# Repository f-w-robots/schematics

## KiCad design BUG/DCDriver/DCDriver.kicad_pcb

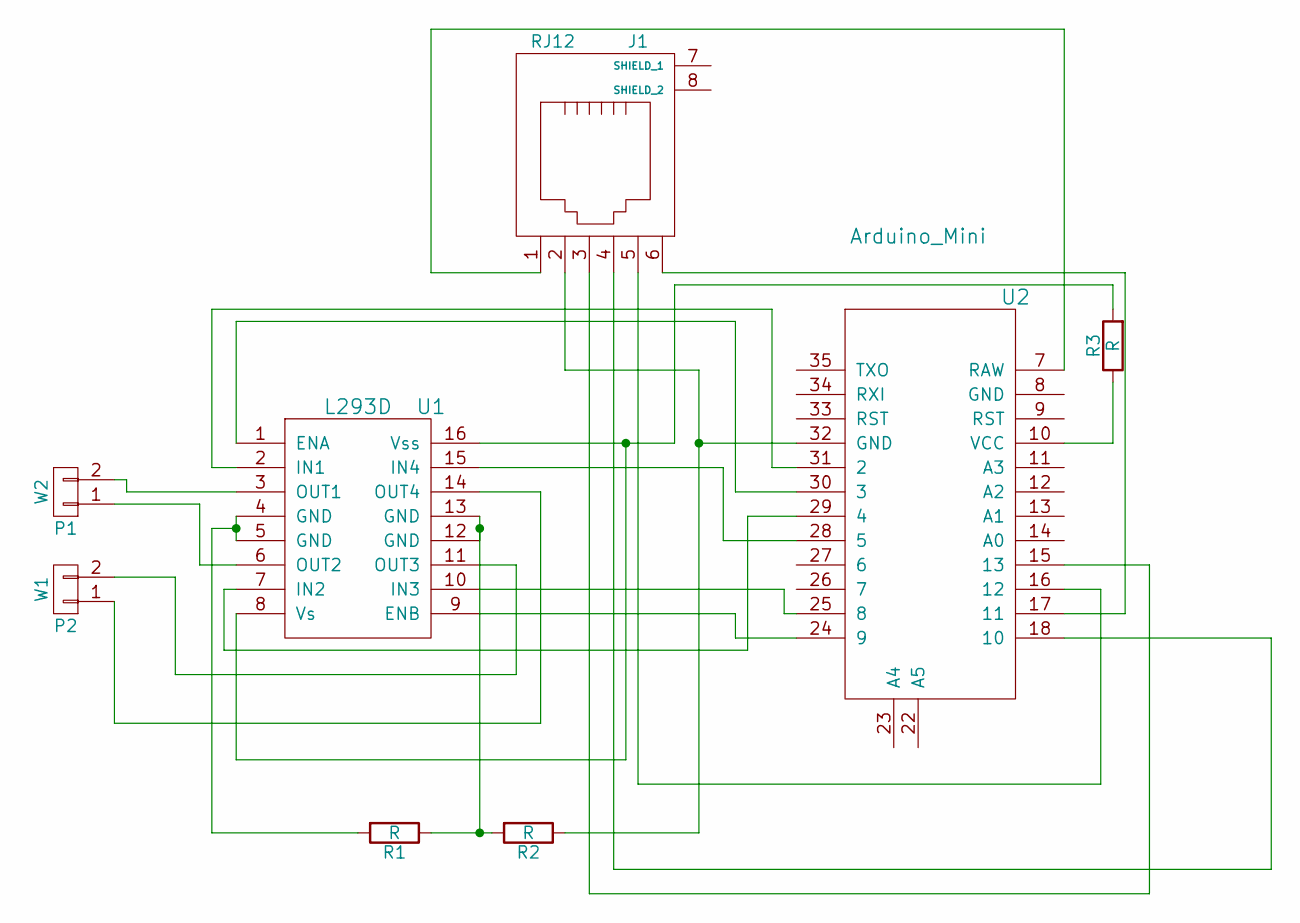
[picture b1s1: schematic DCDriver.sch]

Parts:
J1: RJ12; RJ12_Client
P1: W2; Pin_Header_Straight_1x02
P2: W1; Pin_Header_Straight_1x02
R1, R2, R3: R; R_1206
U1: L293D; DIP-16_W7.62mm
U2: Arduino_Mini; arduino_mini_pro

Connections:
unnamed: J1.1, U2.7 (RAW)
unnamed: J1.2, R2.1, U2.32 (GND)
unnamed: J1.3, U2.15 (13)
unnamed: J1.4, U2.18 (10)
unnamed: J1.5, U2.16 (12)
unnamed: J1.6, U2.17 (11)
unnamed: P1.1, U1.6 (OUT2)
unnamed: P1.2, U1.3 (OUT1)
unnamed: P2.1, U1.14 (OUT4)
unnamed: P2.2, U1.11 (OUT3)
unnamed: R1.1, R2.2, U1.12 (GND), U1.13 (GND)
unnamed: R1.2, U1.4 (GND), U1.5 (GND)
unnamed: R3.1, U2.10 (VCC)
unnamed: R3.2, U1.8 (Vs), U1.16 (Vss)
unnamed: U1.1 (ENA), U2.30 (3)
unnamed: U1.2 (IN1), U2.31 (2)
unnamed: U1.7 (IN2), U2.29 (4)
unnamed: U1.9 (ENB), U2.24 (9)
unnamed: U1.10 (IN3), U2.25 (8)
unnamed: U1.15 (IN4), U2.28 (5)

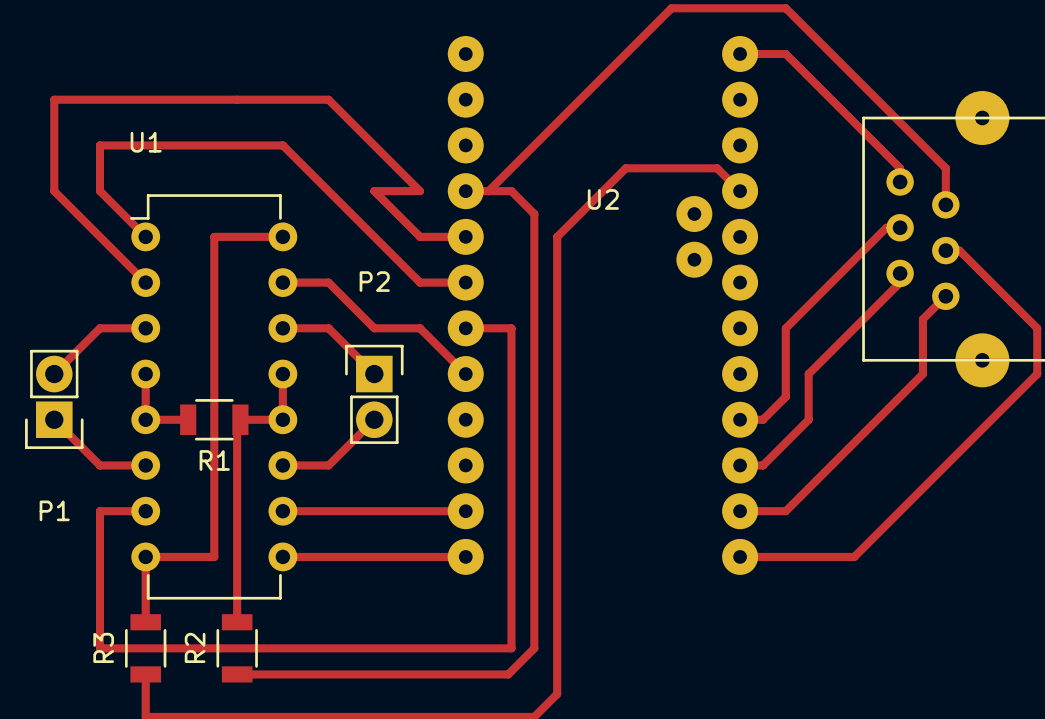
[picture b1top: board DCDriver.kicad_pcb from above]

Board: 2 copper layers, 8 parts (0 on the bottom side), 20 nets.

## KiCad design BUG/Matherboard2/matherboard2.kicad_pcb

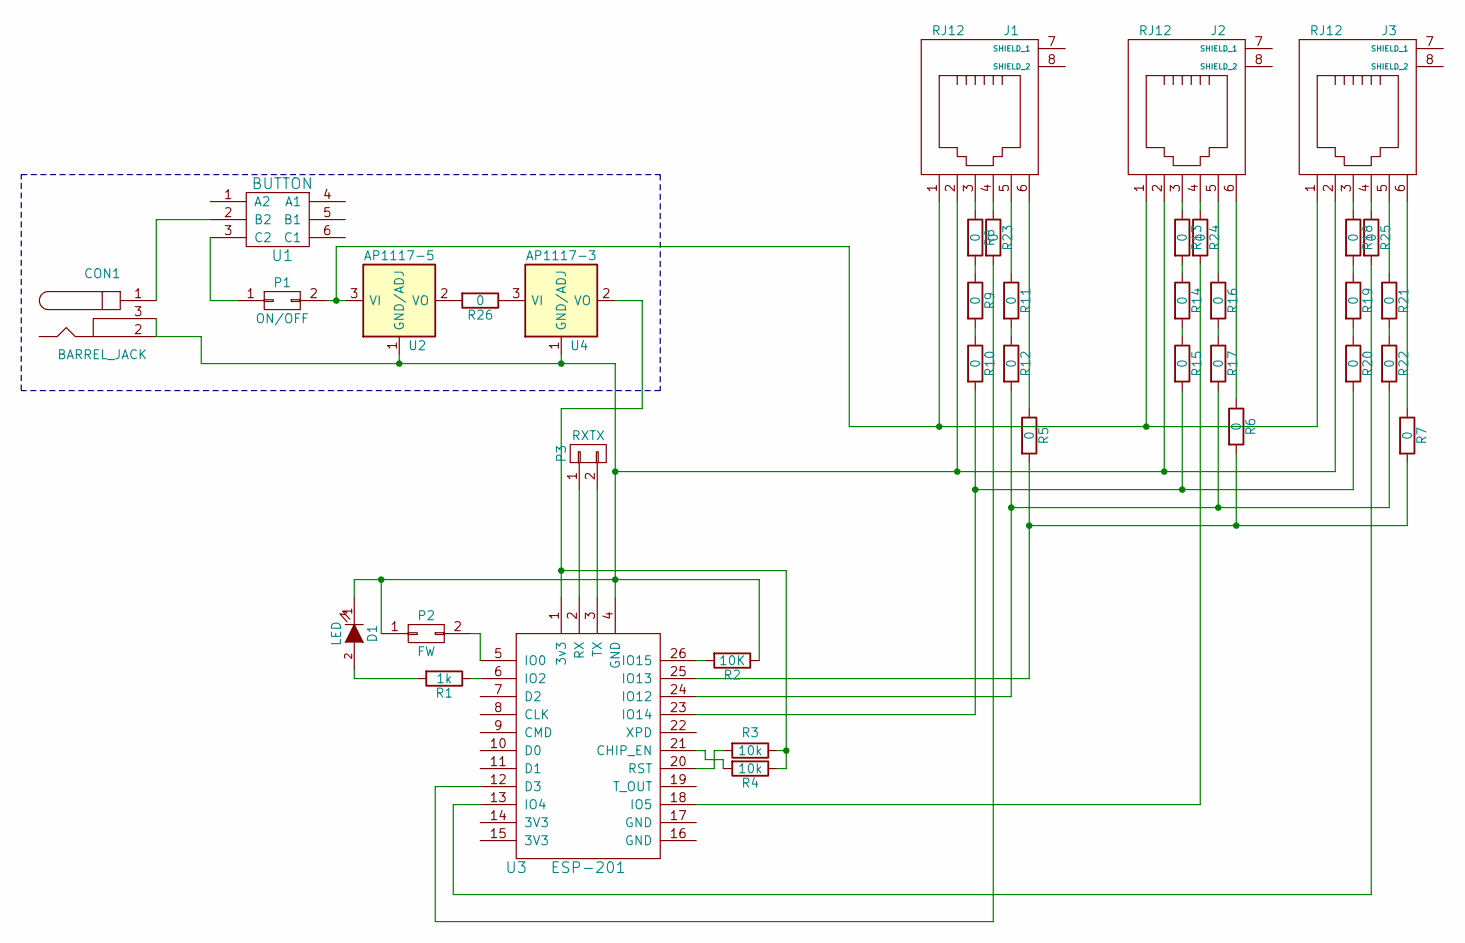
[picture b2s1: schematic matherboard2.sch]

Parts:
CON1: BARREL_JACK
D1: LED; LED-5MM
J1, J2, J3: RJ12; RJ12_E
P1: ON/OFF; Pin_Header_Straight_2x01
P2: FW; Pin_Header_Straight_2x01
P3: RXTX; Pin_Header_Straight_1x02
R1: 1k; Resistor_Horizontal_RM7mm
R2: 10K; Resistor_Horizontal_RM7mm
R3, R4: 10k; Resistor_Horizontal_RM7mm
R5, R6, R7, R8, R9, R10, R11, R12, R13, R14, R15, R16, R17, R18, R19, R20, R21, R22, R23, R24, R25, R26: 0; R_1206
U1: BUTTON; button
U2: AP1117-5; SW_Micro_SPST
U3: ESP-201; ESP201
U4: AP1117-3; SW_Micro_SPST

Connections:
unnamed: CON1.1, U1.2 (B2)
unnamed: CON1.2, CON1.3, D1.1 (K), J1.2, J2.2, J3.2, P2.1, R2.1, U2.1 (GND/ADJ), U3.4 (GND), U4.1 (GND/ADJ)
unnamed: D1.2 (A), R1.2
unnamed: J1.1, J2.1, J3.1, P1.2, U2.3 (VI)
unnamed: J1.3, R8.1
unnamed: J1.4, R23.1
unnamed: J1.5, R11.1
unnamed: J1.6, R5.1
unnamed: J2.3, R13.1
unnamed: J2.4, R24.1
unnamed: J2.5, R16.1
unnamed: J2.6, R6.1
unnamed: J3.3, R18.1
unnamed: J3.4, R25.1
unnamed: J3.5, R21.1
unnamed: J3.6, R7.1
unnamed: P1.1, U1.3 (C2)
unnamed: P2.2, U3.5 (IO0)
unnamed: P3.1, U3.2 (RX)
unnamed: P3.2, U3.3 (TX)
unnamed: R1.1, U3.6 (IO2)
unnamed: R2.2, U3.26 (IO15)
unnamed: R3.1, R4.1, U3.1 (3v3), U4.2 (VO)
unnamed: R3.2, U3.20 (RST)
unnamed: R4.2, U3.21 (CHIP_EN)
unnamed: R5.2, R6.2, R7.2, U3.25 (IO13)
unnamed: R8.2, R9.1
unnamed: R9.2, R10.1
unnamed: R10.2, R15.2, R20.2, U3.23 (IO14)
unnamed: R11.2, R12.1
unnamed: R12.2, R17.2, R22.2, U3.24 (IO12)
unnamed: R13.2, R14.1
unnamed: R14.2, R15.1
unnamed: R16.2, R17.1
unnamed: R18.2, R19.1
unnamed: R19.2, R20.1
unnamed: R21.2, R22.1
unnamed: R23.2, U3.12 (D3)
unnamed: R24.2, U3.18 (IO5)
unnamed: R25.2, U3.13 (IO4)
unnamed: R26.1, U4.3 (VI)
unnamed: R26.2, U2.2 (VO)

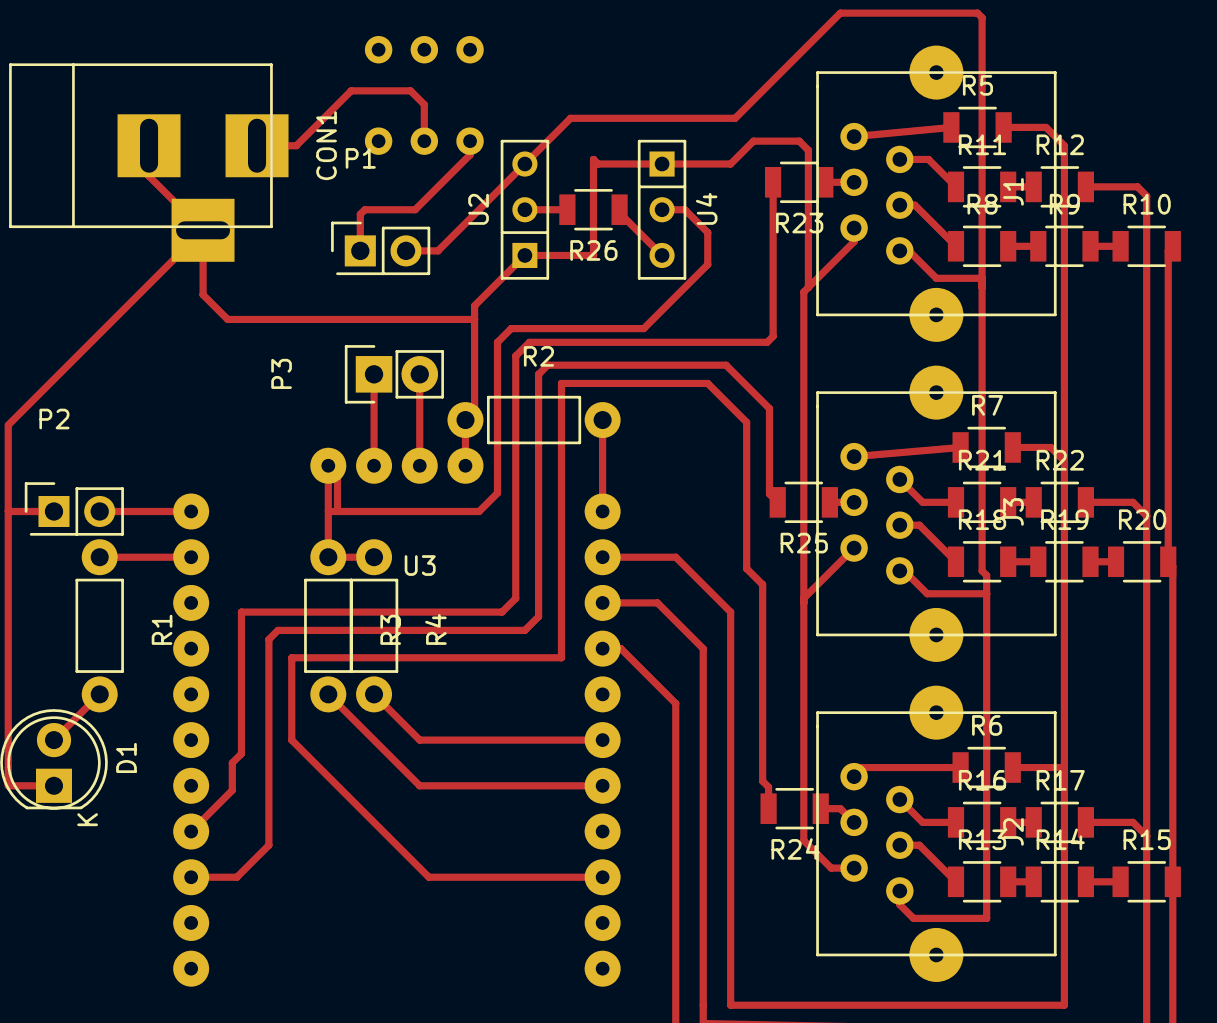
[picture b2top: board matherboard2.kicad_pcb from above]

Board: 2 copper layers, 38 parts (1 on the bottom side), 42 nets.

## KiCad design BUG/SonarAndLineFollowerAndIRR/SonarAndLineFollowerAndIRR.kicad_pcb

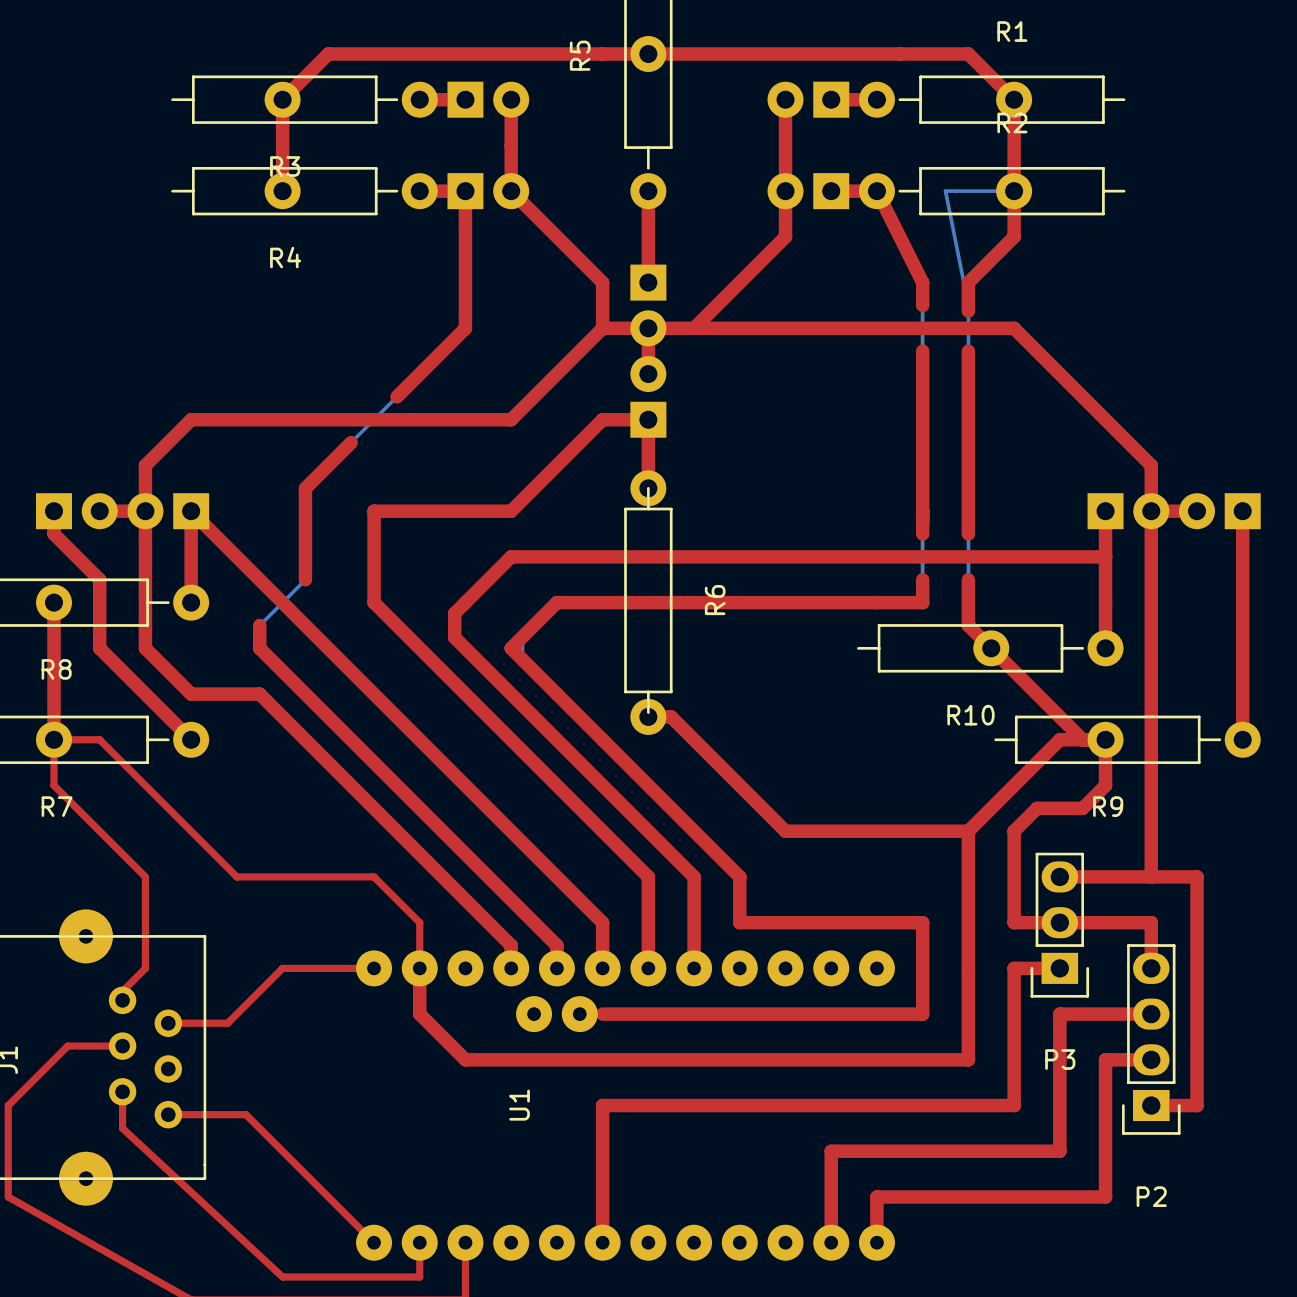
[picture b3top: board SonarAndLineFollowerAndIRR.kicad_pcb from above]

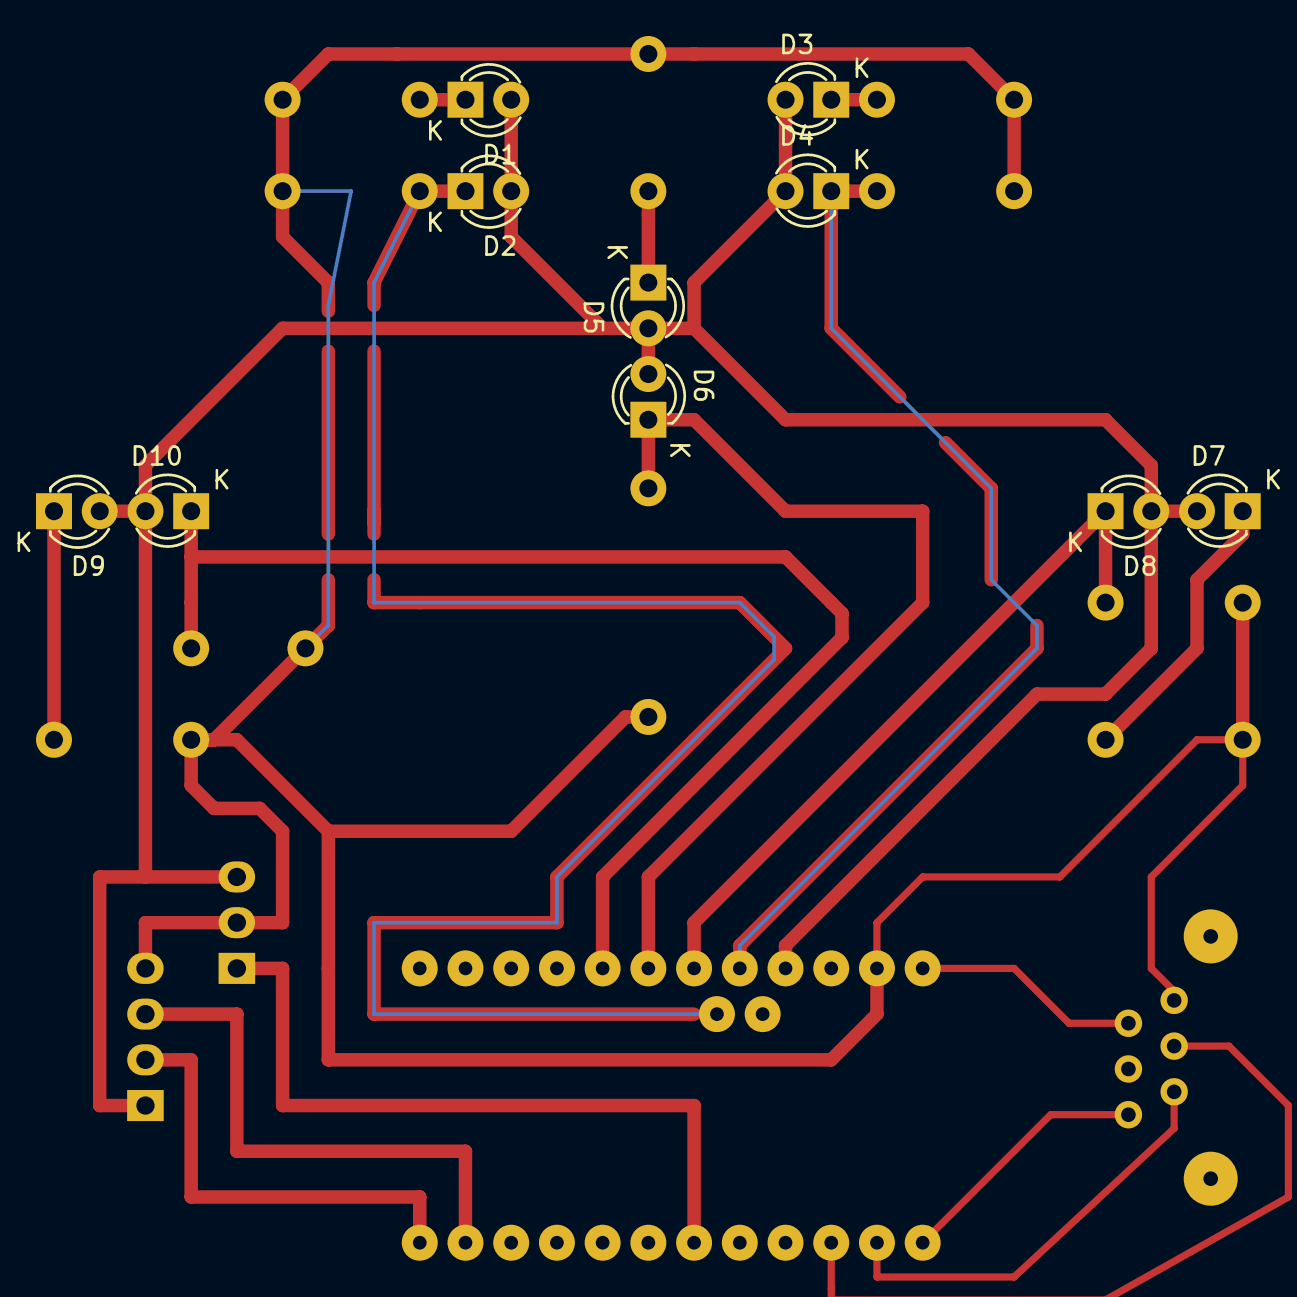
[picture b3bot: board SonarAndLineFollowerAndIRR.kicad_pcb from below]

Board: 2 copper layers, 24 parts (10 on the bottom side), 19 nets.

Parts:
D1, D2, D3, D4, D5, D6, D7, D8, D9, D10: LED; LED-3MM
J1: RJ12; RJ12_Client
P2: Sonar; Pin_Header_Straight_1x04
P3: CONN_01X03; Pin_Header_Straight_1x03
R1, R3, R5, R7, R9: 150; Resistor_Horizontal_RM15mm
R2, R4, R6, R8, R10: 510k; Resistor_Horizontal_RM15mm
U1: Arduino_Mini; arduino_mini_pro

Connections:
unnamed: D1.1, R1.1
unnamed: D1.2, D2.2, D3.2, D4.2, D5.2, D6.2, D7.2, D8.2, D9.2, D10.2, P2.1, P3.3, U1.10
unnamed: D2.1, R2.1, U1.23
unnamed: D3.1, R3.1
unnamed: D4.1, R4.1, U1.11
unnamed: D5.1, R5.1
unnamed: D6.1, R6.1, U1.13
unnamed: D7.1, R7.1
unnamed: D8.1, R8.1, U1.12
unnamed: D9.1, R9.1
unnamed: D10.1, R10.1, U1.14
unnamed: J1.1, U1.35
unnamed: J1.2, U1.34
unnamed: J1.4, U1.33
unnamed: J1.5, U1.7
unnamed: J1.6, P2.4, P3.2, R1.2, R2.2, R3.2, R4.2, R5.2, R6.2, R7.2, R8.2, R9.2, R10.2, U1.8
unnamed: P2.2, U1.24
unnamed: P2.3, U1.25
unnamed: P3.1, U1.30

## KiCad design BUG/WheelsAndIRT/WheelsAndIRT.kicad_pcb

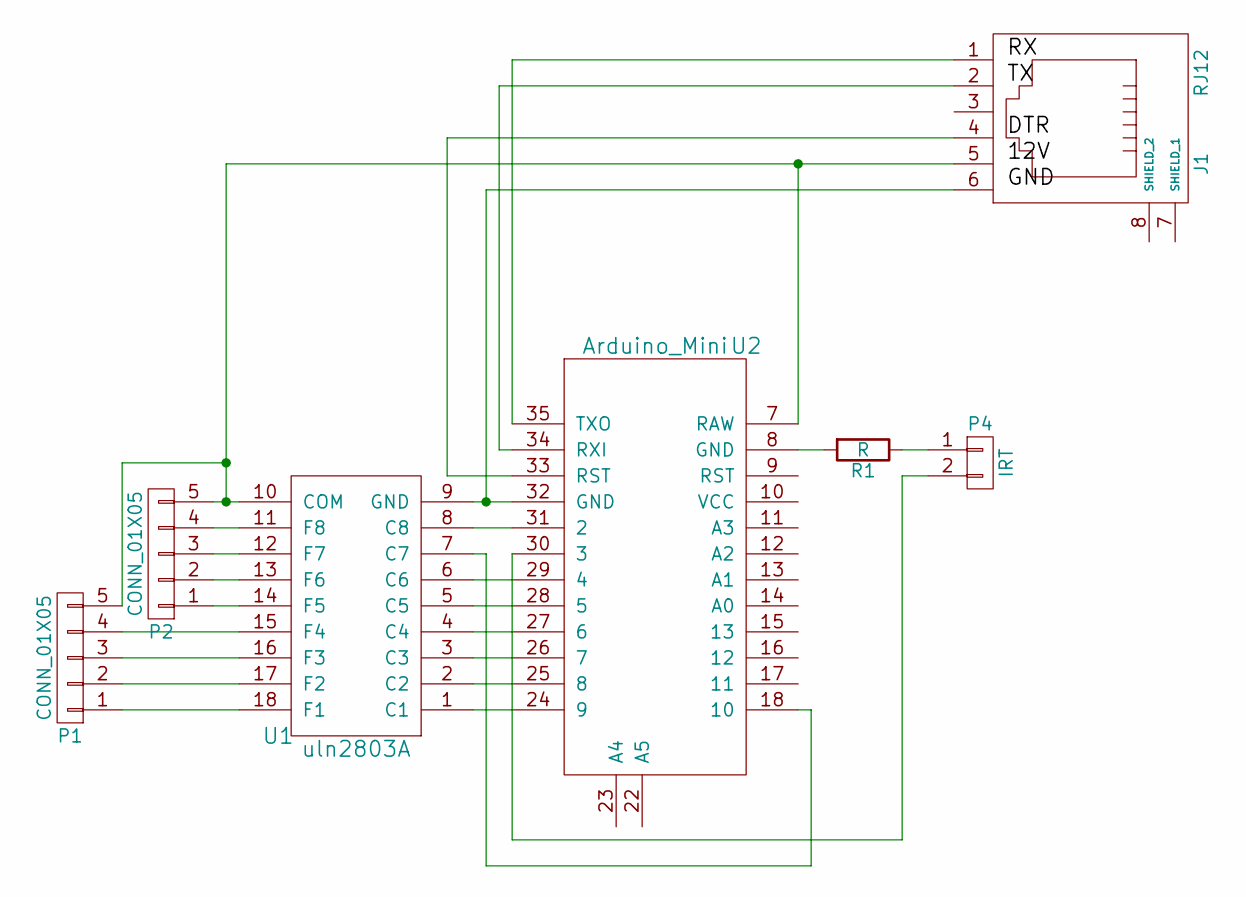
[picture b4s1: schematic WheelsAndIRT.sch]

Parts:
J1: RJ12; RJ12_Client
P1, P2: CONN_01X05; Pin_Header_Straight_1x05
P4: IRT; Pin_Header_Straight_1x02
R1: R; Resistor_Horizontal_RM10mm
U1: uln2803A; DIP-18_W7.62mm
U2: Arduino_Mini; arduino_mini_pro

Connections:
unnamed: J1.1, U2.35 (TXO)
unnamed: J1.2, U2.34 (RXI)
unnamed: J1.4, U2.33 (RST)
unnamed: J1.5, P1.5, P2.5, U1.10 (COM), U2.7 (RAW)
unnamed: J1.6, U1.9 (GND), U2.32 (GND)
unnamed: P1.1, U1.18 (F1)
unnamed: P1.2, U1.17 (F2)
unnamed: P1.3, U1.16 (F3)
unnamed: P1.4, U1.15 (F4)
unnamed: P2.1, U1.14 (F5)
unnamed: P2.2, U1.13 (F6)
unnamed: P2.3, U1.12 (F7)
unnamed: P2.4, U1.11 (F8)
unnamed: P4.1, R1.1
unnamed: P4.2, U2.30 (3)
unnamed: R1.2, U2.8 (GND)
unnamed: U1.1 (C1), U2.24 (9)
unnamed: U1.2 (С2), U2.25 (8)
unnamed: U1.3 (С3), U2.26 (7)
unnamed: U1.4 (С4), U2.27 (6)
unnamed: U1.5 (С5), U2.28 (5)
unnamed: U1.6 (С6), U2.29 (4)
unnamed: U1.7 (С7), U2.18 (10)
unnamed: U1.8 (С8), U2.31 (2)

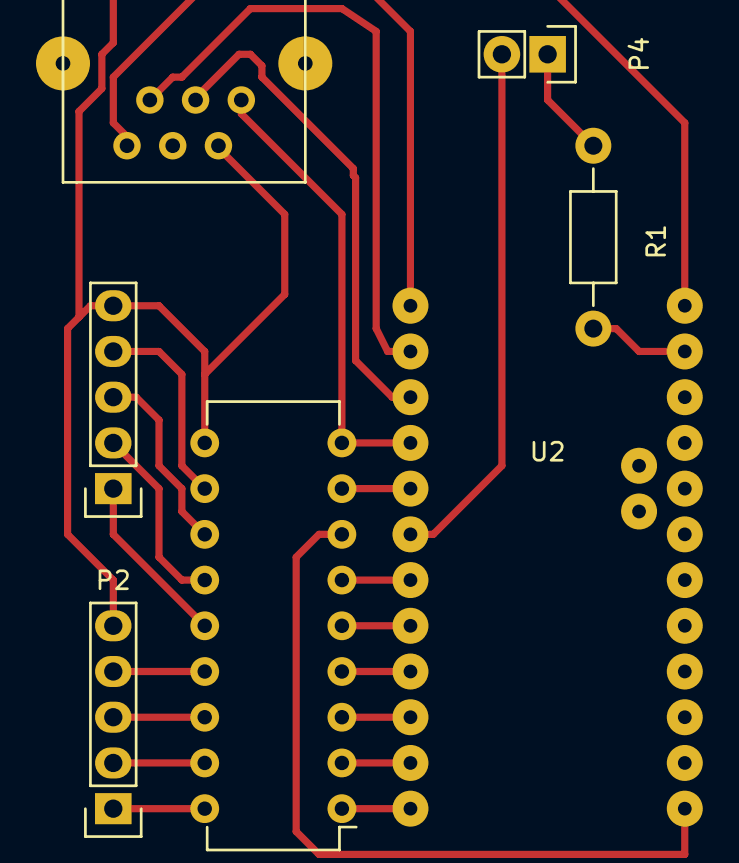
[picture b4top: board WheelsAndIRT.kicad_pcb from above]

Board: 2 copper layers, 7 parts (0 on the bottom side), 24 nets.

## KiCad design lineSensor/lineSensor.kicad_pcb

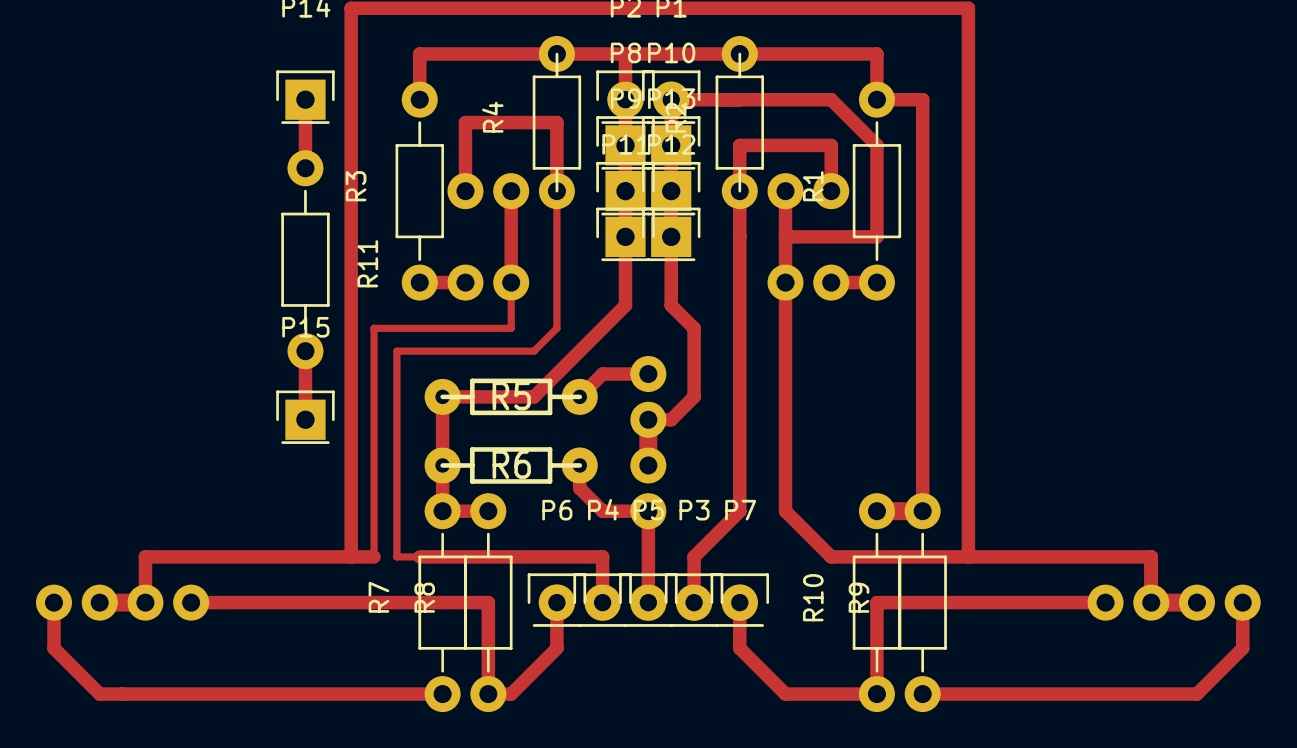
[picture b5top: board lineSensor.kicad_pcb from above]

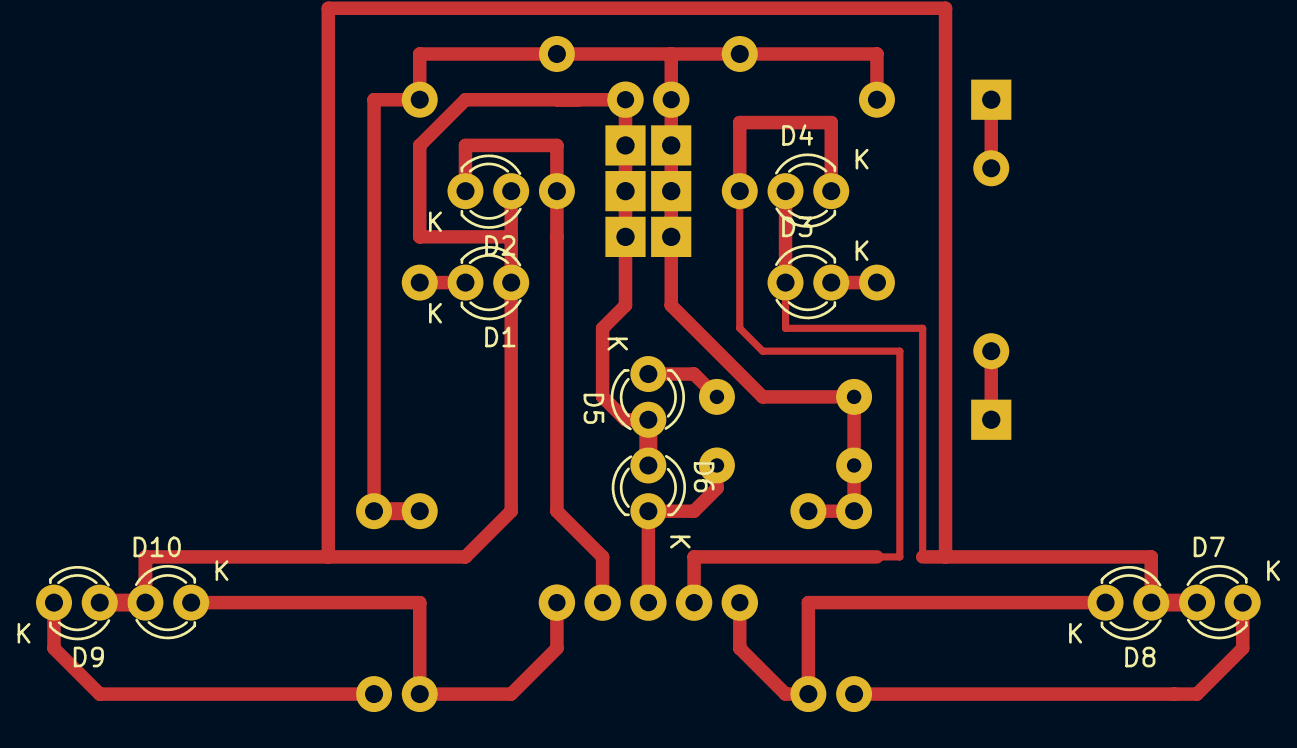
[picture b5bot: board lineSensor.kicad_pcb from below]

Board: 2 copper layers, 36 parts (10 on the bottom side), 14 nets.

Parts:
D1, D2, D3, D4, D5, D6, D7, D8, D9, D10: LED; LED-3MM
P1, P2, P3, P4, P5, P6, P7, P8, P9, P10, P11, P12, P13, P14, P15: CONN_01X01; Pin_Header_Straight_1x01
R1, R3, R7, R9: 150; Resistor_Horizontal_RM10mm
R2, R4, R8, R10: 510k; Resistor_Horizontal_RM10mm
R5: 150; RC03
R6: 510k; RC03
R11: 8k2; Resistor_Horizontal_RM10mm

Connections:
unnamed: D1.1, R1.1
unnamed: D1.2, D2.2, D3.2, D4.2, D5.2, D6.2, D7.2, D8.2, D9.2, D10.2, P1.1, P10.1, P12.1, P13.1
unnamed: D2.1, P3.1, R2.1
unnamed: D3.1, R3.1
unnamed: D4.1, P4.1, R4.1
unnamed: D5.1, R5.1
unnamed: D6.1, P5.1, R6.1
unnamed: D7.1, R7.1
unnamed: D8.1, P6.1, R8.1
unnamed: D9.1, R9.1
unnamed: D10.1, P7.1, R10.1
unnamed: P2.1, P8.1, P9.1, P11.1, R1.2, R2.2, R3.2, R4.2, R5.2, R6.2, R7.2, R8.2, R9.2, R10.2
unnamed: P14.1, R11.1
unnamed: P15.1, R11.2

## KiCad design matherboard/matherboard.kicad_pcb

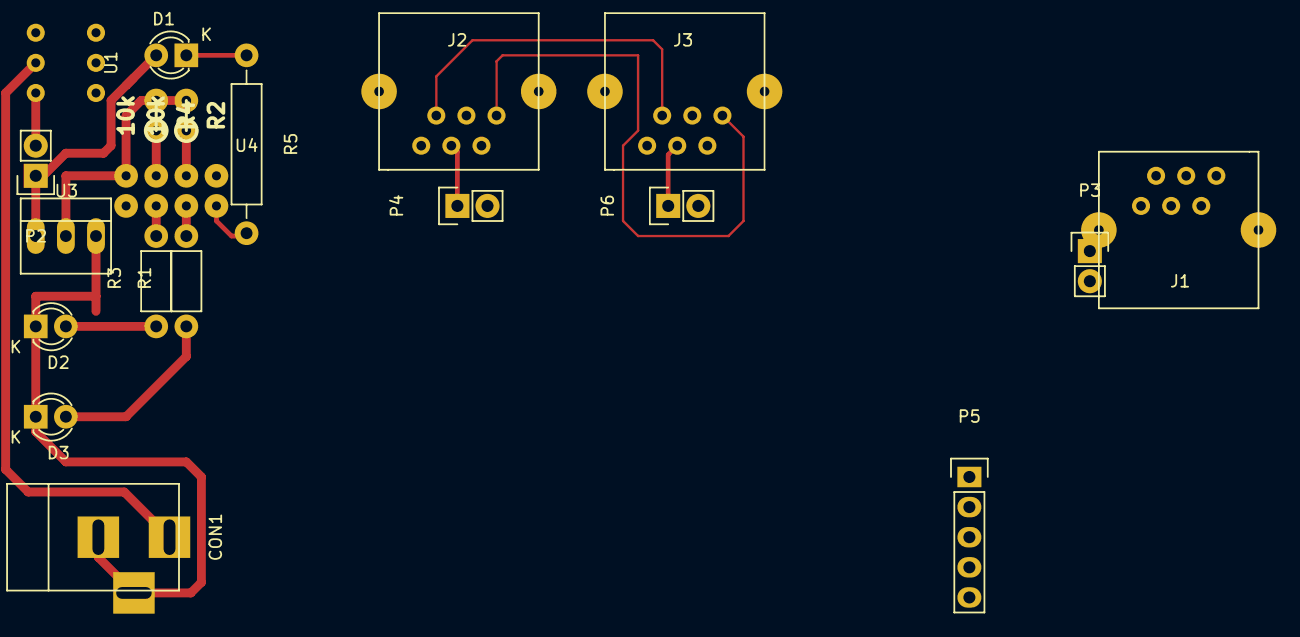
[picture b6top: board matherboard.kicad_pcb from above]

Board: 2 copper layers, 20 parts (0 on the bottom side), 18 nets.

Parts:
CON1: BARREL_JACK
D1, D2, D3: LED; LED-3MM
J1, J2, J3: RJ12; RJ12_E
P2, P3, P4, P6: CONN_01X02; Pin_Header_Straight_1x02
P5: CONN_01X05; Pin_Header_Straight_1x05
R1, R3: 1k; Resistor_Horizontal_RM7mm
R2, R4: 10k; rc03_vert
R5: 500; Resistor_Horizontal_RM15mm
U1: button
U3: STAB3.3; PINHEAD1-3
U4: ESP8266; esp8266

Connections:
unnamed: CON1.1, U1.5
unnamed: CON1.2, CON1.3, D2.1, D3.1, J1.6, J2.6, J3.6, P5.1, R5.2, U3.3, U4.5
unnamed: D1.1, R5.1
unnamed: D1.2, J1.5, J2.5, J3.5, P2.1, U3.1
unnamed: D2.2, R3.1
unnamed: D3.2, R1.1
unnamed: J1.1, J2.1, J3.1, P5.4, U4.8
unnamed: J1.2, J2.2, J3.2, P5.3, U4.4
unnamed: J1.4, P3.1
unnamed: J2.4, P4.1
unnamed: J3.4, P6.1
unnamed: P2.2, U1.6
unnamed: P3.2, P4.2, P5.2, P6.2
unnamed: R1.2, U4.6
unnamed: R2.1, U4.3
unnamed: R2.2, R4.2, U3.2, U4.1
unnamed: R3.2, U4.7
unnamed: R4.1, U4.2
